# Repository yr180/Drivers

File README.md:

# Drivers
This Project includes eagle files for various DC motor drivers

#VNH2SP30:
Pin sequence for logic input:
   1. 5 V
   2. EN
   3. IN A
   4. IN B
   5. PWM
   6. CS
   7. GND
   
  • Vcc(max): 41 V
  • Iout(max): 30 A
  • PWM freq: upto 20 KHz
  • Circuit provides reverse battery protection
  • Thermal shutdown (typical) at 175 °C
  • LEDs for logic indication

#L293D

#L298

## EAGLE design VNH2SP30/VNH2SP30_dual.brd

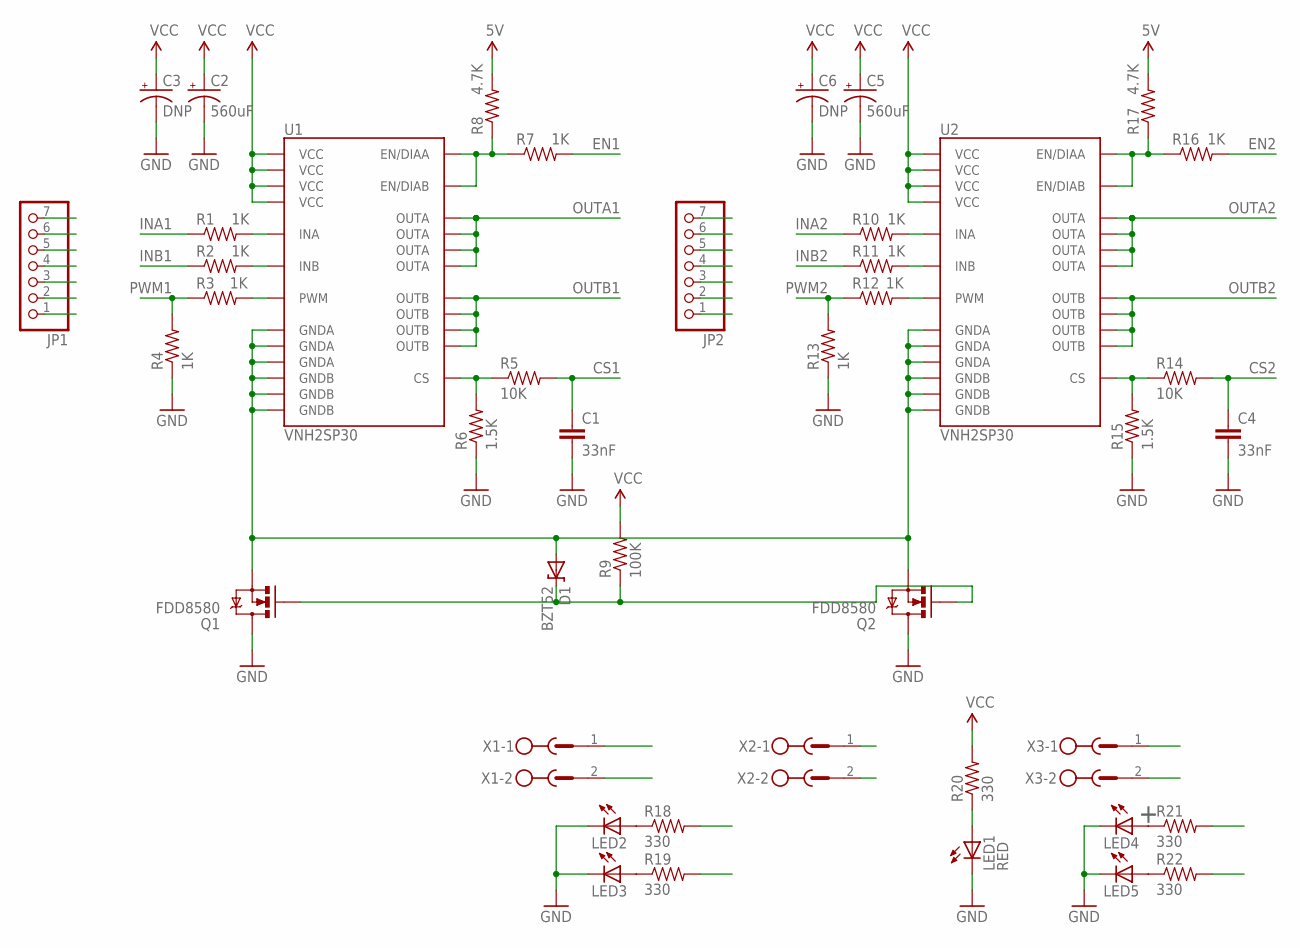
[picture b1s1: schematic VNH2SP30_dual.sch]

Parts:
C1, C4: 33nF; 1206
C2, C5: 560uF; PANASONIC_G
C3, C6: DNP; CPOL-RADIAL-1000UF-25V
D1: BZT52; SMB-DIODE
JP1, JP2: PINHD-1X7; 1X07
LED1: RED; CHIPLED_1206
LED2, LED3, LED4, LED5: GREEN; CHIPLED_1206
Q1, Q2: FDD8580; DPAK
R1, R2, R3, R4, R7, R10, R11, R12, R13, R16: 1K; 1206
R5, R14: 10K; 1206
R6, R15: 1.5K; 1206
R8, R17: 4.7K; 1206
R9: 100K; 1206
R18, R19, R20, R21, R22: 330; 1206
U1, U2: VNH2SP30
X1, X2, X3: MSTBV2

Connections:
5V: JP1.7, JP2.7, R8.2, R17.2
CS1: C1.1, JP1.2, R5.2
CS2: C4.1, JP2.2, R14.2
EN1: JP1.6, R7.2
EN2: JP2.6, R16.2
GND: C1.2, C2.-, C3.2 (-), C4.2, C5.-, C6.2 (-), JP1.1, JP2.1, LED1.C, LED2.C, LED3.C, LED4.C, LED5.C, Q1.4 (D), Q2.4 (D), R4.1, R6.1, R13.1, R15.1, X2.1
INA1: JP1.5, R1.1
INA2: JP2.5, R10.1
INB1: JP1.4, R2.1
INB2: JP2.4, R11.1
unnamed: R2.2, U1.11 (INB)
unnamed: R1.2, U1.5 (INA)
unnamed: R11.2, U2.11 (INB)
unnamed: R10.2, U2.5 (INA)
unnamed: R3.2, U1.8 (PWM)
unnamed: R12.2, U2.8 (PWM)
unnamed: R5.1, R6.2, U1.9 (CS)
unnamed: R14.1, R15.2, U2.9 (CS)
unnamed: R16.1, R17.1, U2.6 (EN/DIAA), U2.10 (EN/DIAB)
unnamed: D1.A, Q1.3 (S), Q2.3 (S), U1.18 (GNDB), U1.19 (GNDB), U1.20 (GNDB), U1.26 (GNDA), U1.27 (GNDA), U1.28 (GNDA), U2.18 (GNDB), U2.19 (GNDB), U2.20 (GNDB), U2.26 (GNDA), U2.27 (GNDA), U2.28 (GNDA)
unnamed: R7.1, R8.1, U1.6 (EN/DIAA), U1.10 (EN/DIAB)
unnamed: D1.C, Q1.1 (G), Q2.1 (G), R9.1
unnamed: LED1.A, R20.1
unnamed: LED2.A, R18.1
unnamed: LED3.A, R19.1
unnamed: LED4.A, R21.1
unnamed: LED5.A, R22.1
OUTA1: R18.2, U1.1 (OUTA), U1.25 (OUTA), U1.30 (OUTA), U1.SLUG3 (OUTA), X1.1
OUTA2: R22.2, U2.1 (OUTA), U2.25 (OUTA), U2.30 (OUTA), U2.SLUG3 (OUTA), X3.1
OUTB1: R19.2, U1.15 (OUTB), U1.16 (OUTB), U1.21 (OUTB), U1.SLUG2 (OUTB), X1.2
OUTB2: R21.2, U2.15 (OUTB), U2.16 (OUTB), U2.21 (OUTB), U2.SLUG2 (OUTB), X3.2
PWM1: JP1.3, R3.1, R4.2
PWM2: JP2.3, R12.1, R13.2
VCC: C2.+, C3.1 (+), C5.+, C6.1 (+), R9.2, R20.2, U1.3 (VCC), U1.13 (VCC), U1.23 (VCC), U1.SLUG1 (VCC), U2.3 (VCC), U2.13 (VCC), U2.23 (VCC), U2.SLUG1 (VCC), X2.2

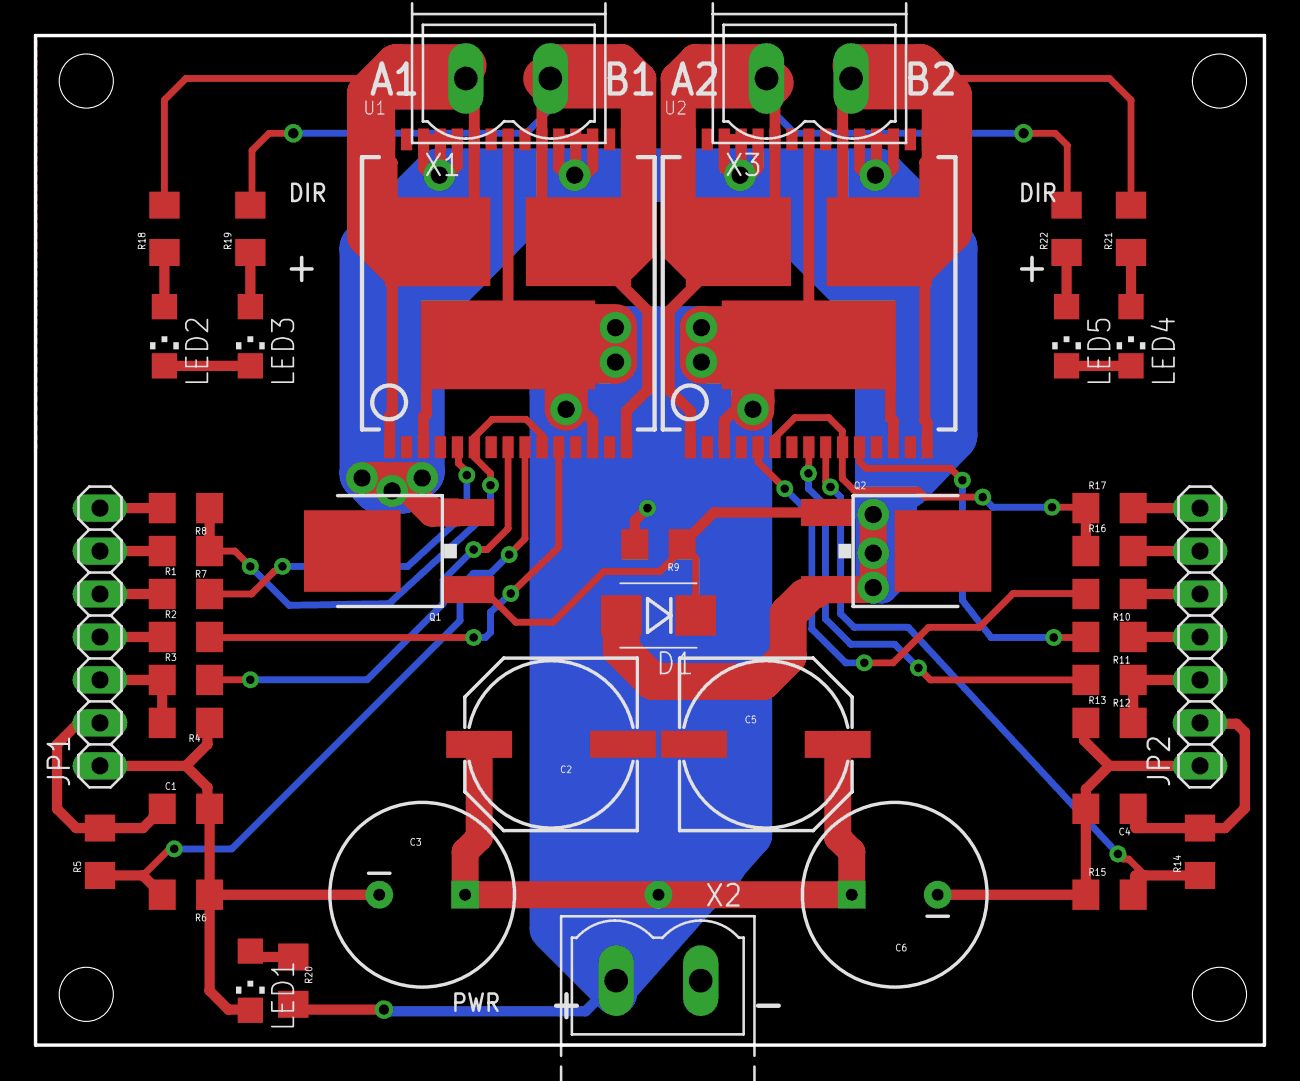
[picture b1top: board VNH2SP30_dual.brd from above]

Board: 2 copper layers, 72.7 x 59.7 mm, 43 parts (0 on the bottom side), 34 nets.

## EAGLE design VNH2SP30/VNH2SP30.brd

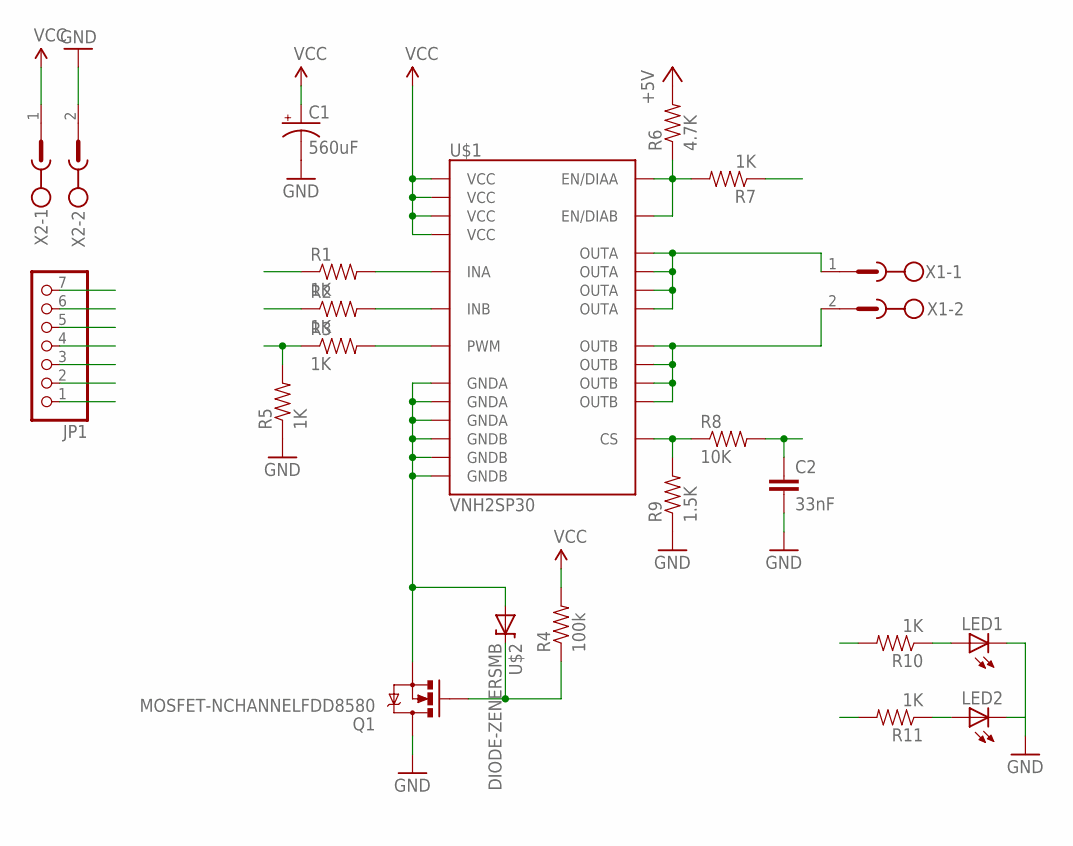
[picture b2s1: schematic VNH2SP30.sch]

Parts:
C1: 560uF; PANASONIC_G
C2: 33nF; 1206
JP1: PINHD-1X7; 1X07
LED1, LED2: LEDCHIPLED_1206; CHIPLED_1206
Q1: MOSFET-NCHANNELFDD8580; DPAK
R1, R2, R3, R5, R7, R10, R11: 1K; 1206
R4: 100k; 1206
R6: 4.7K; 1206
R8: 10K; 1206
R9: 1.5K; 1206
U$1: VNH2SP30
U$2: DIODE-ZENERSMB; SMB-DIODE
X1, X2: MSTBV2

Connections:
+5V: JP1.7, R6.2
CS: C2.1, JP1.2, R8.2
EN: JP1.6, R7.1
GND: C1.-, C2.2, JP1.1, LED1.C, LED2.C, Q1.4 (D), R5.1, R9.1, X2.2
INA: JP1.5, R1.1
INB: JP1.4, R2.1
unnamed: Q1.3 (S), U$1.18 (GNDB), U$1.19 (GNDB), U$1.20 (GNDB), U$1.26 (GNDA), U$1.27 (GNDA), U$1.28 (GNDA), U$2.A
unnamed: R1.2, U$1.5 (INA)
unnamed: R2.2, U$1.11 (INB)
unnamed: R3.2, U$1.8 (PWM)
unnamed: Q1.1 (G), R4.1, U$2.C
unnamed: R8.1, R9.2, U$1.9 (CS)
unnamed: R6.1, R7.2, U$1.6 (EN/DIAA), U$1.10 (EN/DIAB)
unnamed: LED2.A, R11.1
unnamed: LED1.A, R10.1
OUTA: R11.2, U$1.1 (OUTA), U$1.25 (OUTA), U$1.30 (OUTA), U$1.SLUG3 (OUTA), X1.1
OUTB: R10.2, U$1.15 (OUTB), U$1.16 (OUTB), U$1.21 (OUTB), U$1.SLUG2 (OUTB), X1.2
PWM: JP1.3, R3.1, R5.2
VCC: C1.+, R4.2, U$1.3 (VCC), U$1.13 (VCC), U$1.23 (VCC), U$1.SLUG1 (VCC), X2.1

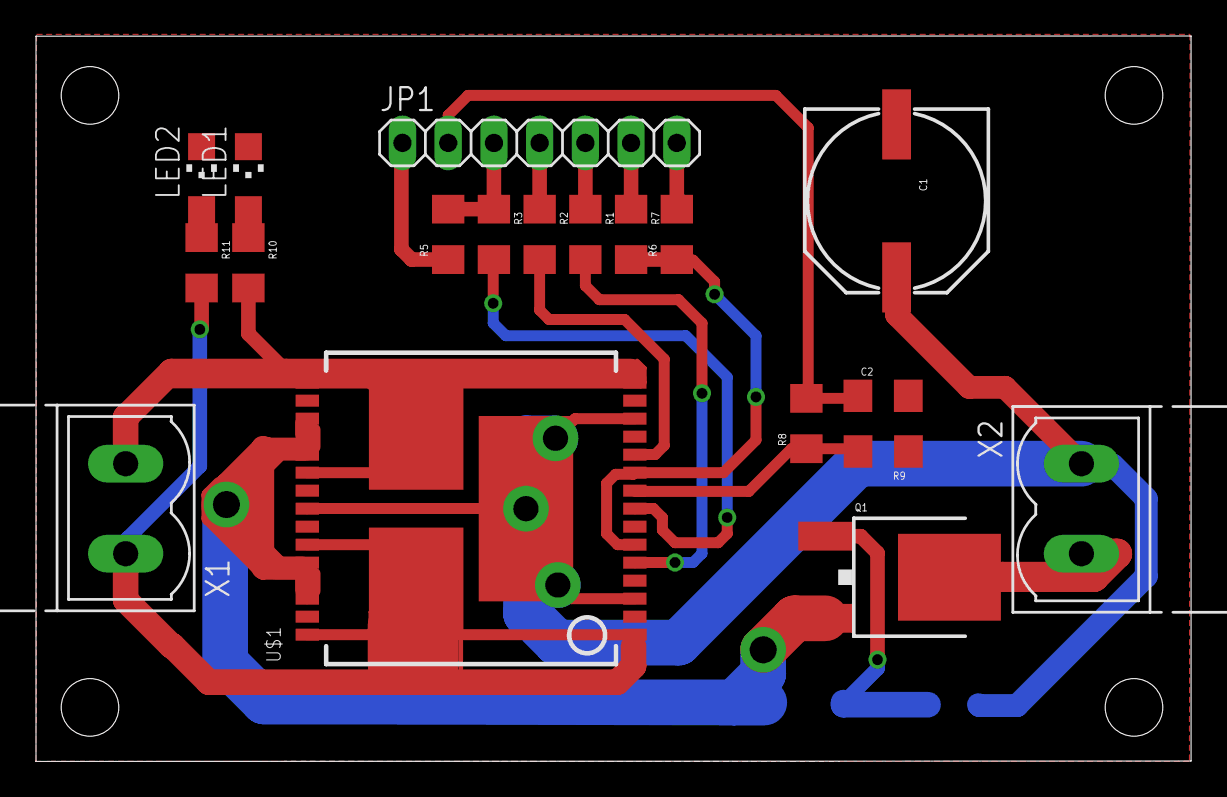
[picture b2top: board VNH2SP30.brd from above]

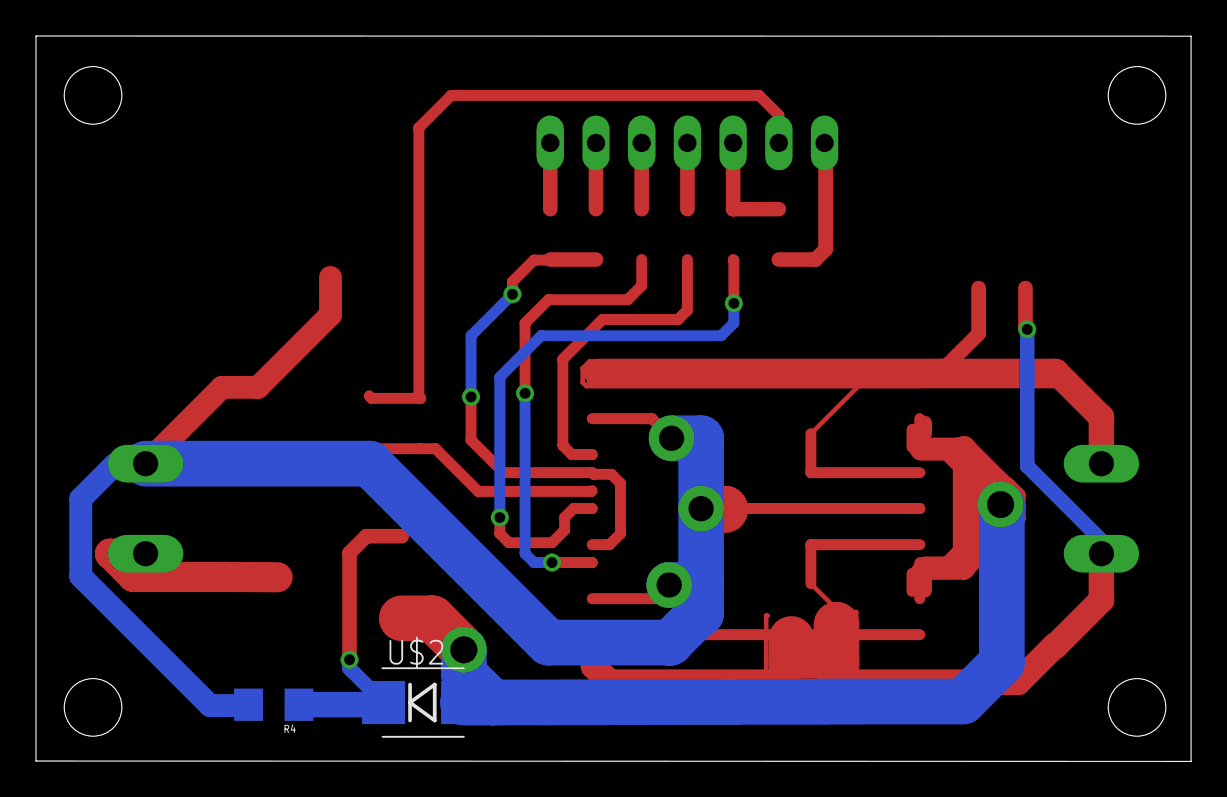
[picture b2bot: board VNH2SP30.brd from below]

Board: 2 copper layers, 64.2 x 40.3 mm, 21 parts (2 on the bottom side), 19 nets.

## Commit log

2017-04-19 Rename VNH2SP30e.brd to VNH2SP30.brd
2017-04-19 Rename VNH2SP30e.sch to VNH2SP30.sch
2017-04-27 Create abc
